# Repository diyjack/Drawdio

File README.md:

# Drawdio
Drawdio is an electronic pencil that makes music while you draw.
Essentially, it's a simple musical synthesizer that uses the conductive properties of pencil graphite to create different sounds.
The original design/idea is from [Jay Silver](http://www.drawdio.com).

Shop: [Drawdio](http://www.watterott.com/en/Drawdio-Kit)

Assembly Instructions: 
[English](https://raw.github.com/watterott/Drawdio/master/pcb/Drawdio_en.pdf), 
[German](https://raw.github.com/watterott/Drawdio/master/pcb/Drawdio_de.pdf), 
[Italian](https://raw.github.com/watterott/Drawdio/master/pcb/Drawdio_it.pdf)

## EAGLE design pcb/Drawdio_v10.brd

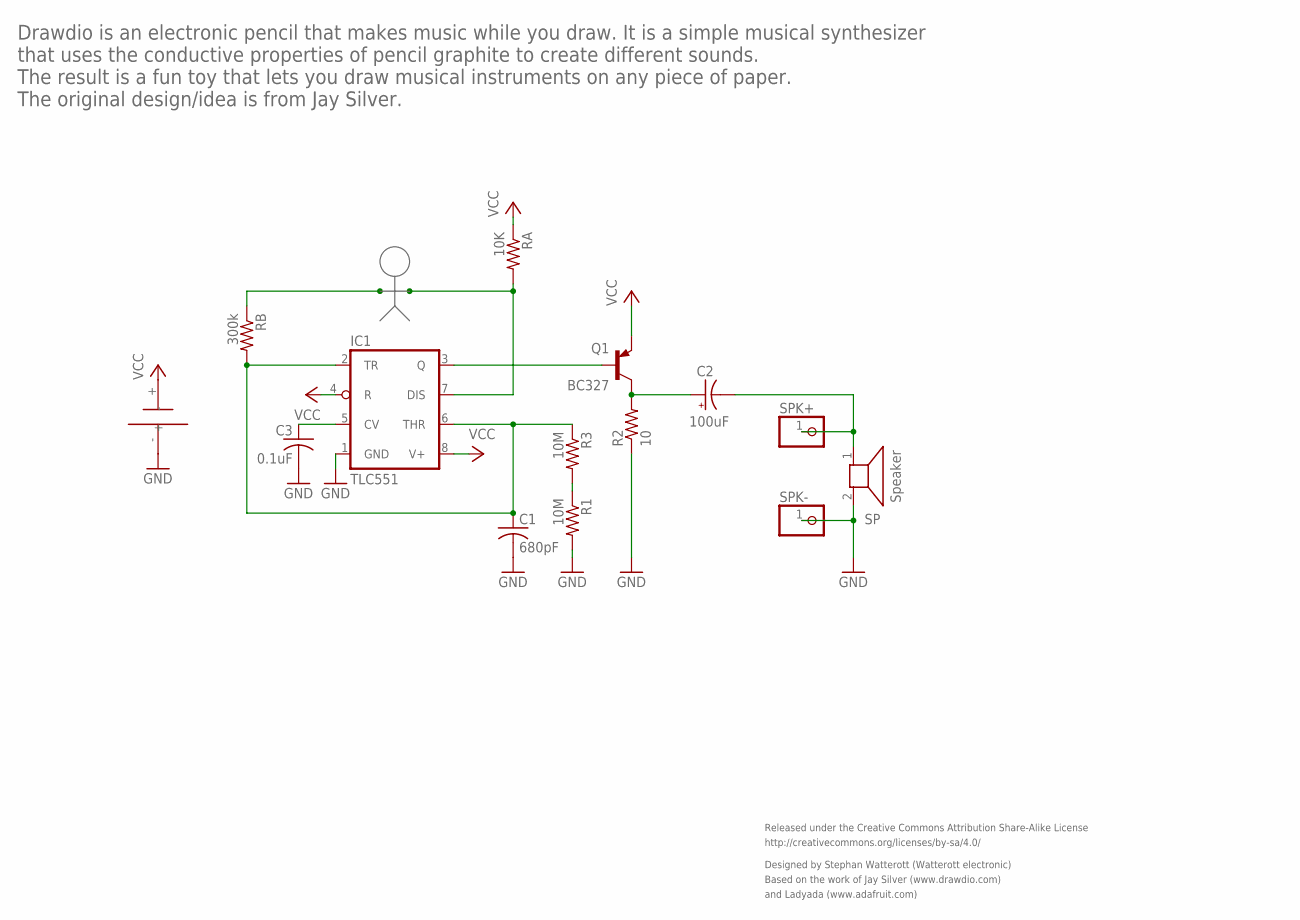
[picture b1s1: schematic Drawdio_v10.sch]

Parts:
C1: 680pF; C025-025X050
C2: 100uF; E2,5-5
C3: 0.1uF; C025-025X050
IC1: TLC551; DIL08
Q1: BC327; TO92-CBE
R1, R3: 10M; 0207/10
R2: 10; 0207/10
RA: 10K; 0207/10
RB: 300k; 0207/10
SP: Speaker; PS603
SPK+: PINHD-1X1; 1X01
SPK-: PINHD-1X1; 1X01
U$1: AAA

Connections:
GND: C1.2, C3.2, IC1.1 (GND), R1.2, R2.1, SP.2, SPK-.1, U$1.-
unnamed: C3.1, IC1.5 (CV)
unnamed: IC1.3 (Q), Q1.B
unnamed: C2.+, Q1.C, R2.2
unnamed: C1.1, IC1.2 (TR), IC1.6 (THR), R3.1, RB.2
unnamed: IC1.7 (DIS), RA.2
unnamed: C2.-, SP.1, SPK+.1
unnamed: R1.1, R3.2
VCC: IC1.4 (R), IC1.8 (V+), Q1.E, RA.1, U$1.+

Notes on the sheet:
Released under the Creative Commons Attribution Share-Alike License
http://creativecommons.org/licenses/by-sa/4.0/
Designed by Stephan Watterott (Watterott electronic)
Based on the work of Jay Silver (www.drawdio.com)
Drawdio is an electronic pencil that makes music while you draw. It is a simple musical synthesizer that uses the conductive properties of pencil graphite to create different sounds. The result is a fun toy that lets you draw musical instruments on any piece of paper. The original design/idea is fr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
and Ladyada (www.adafruit.com)

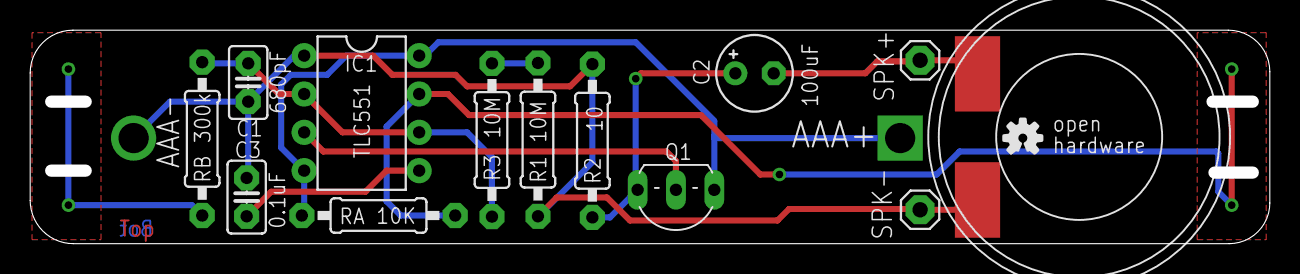
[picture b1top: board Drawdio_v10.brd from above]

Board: 2 copper layers, 81.3 x 13.3 mm, 15 parts (1 on the bottom side), 9 nets.

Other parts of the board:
U$2: WE-LOGO

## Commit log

2013-09-19 added schematic and layout
2013-09-19 added assembly instructions
2013-09-19 added image
2013-09-20 updated schematics
2013-09-27 updated assembly instructions
2014-04-08 updated license information
2014-08-21 updated layout and schematics
2014-11-06 cleaned up schematics and layout
2015-01-10 moved image
